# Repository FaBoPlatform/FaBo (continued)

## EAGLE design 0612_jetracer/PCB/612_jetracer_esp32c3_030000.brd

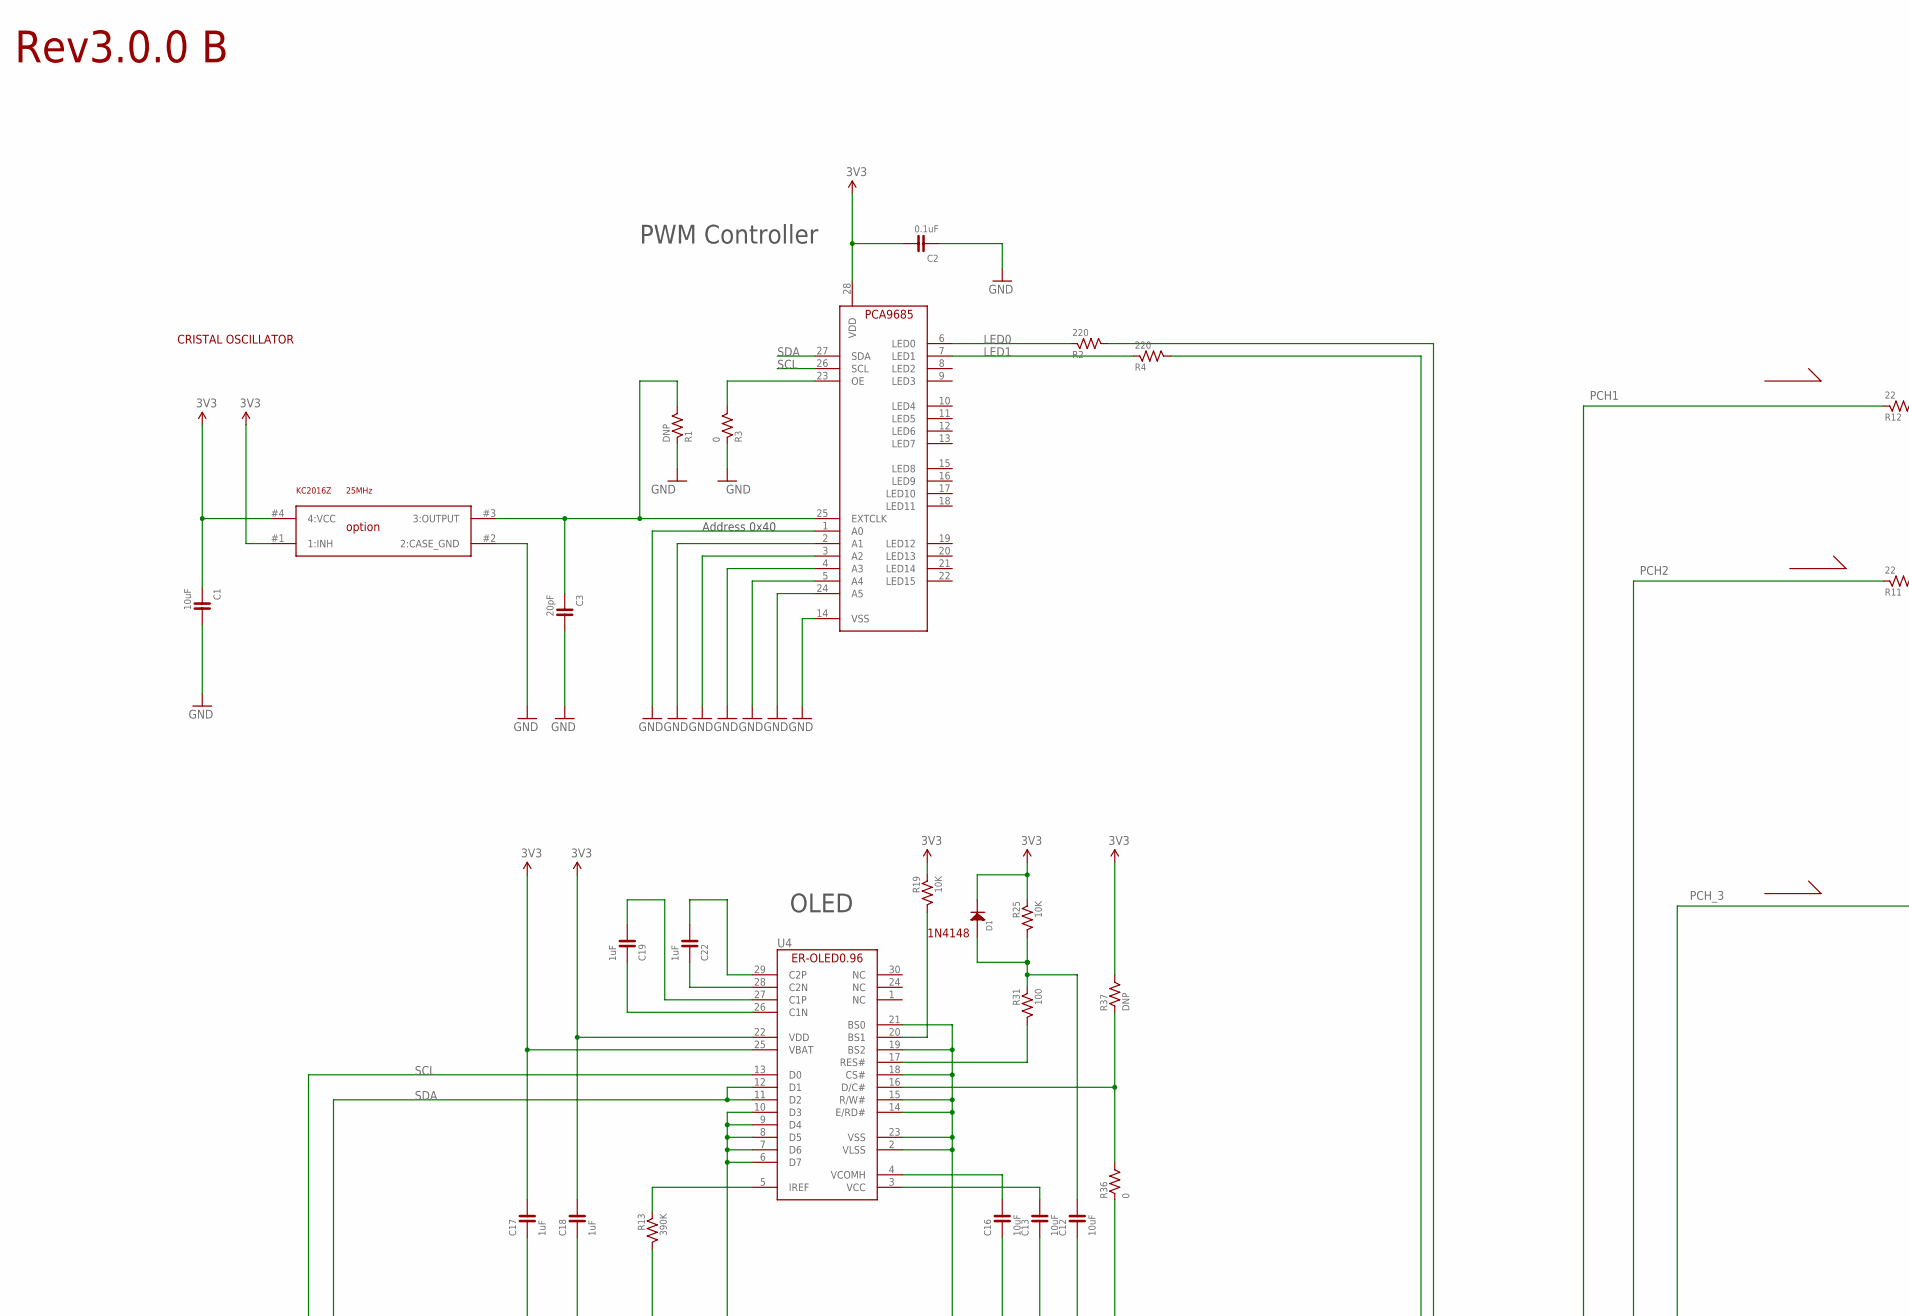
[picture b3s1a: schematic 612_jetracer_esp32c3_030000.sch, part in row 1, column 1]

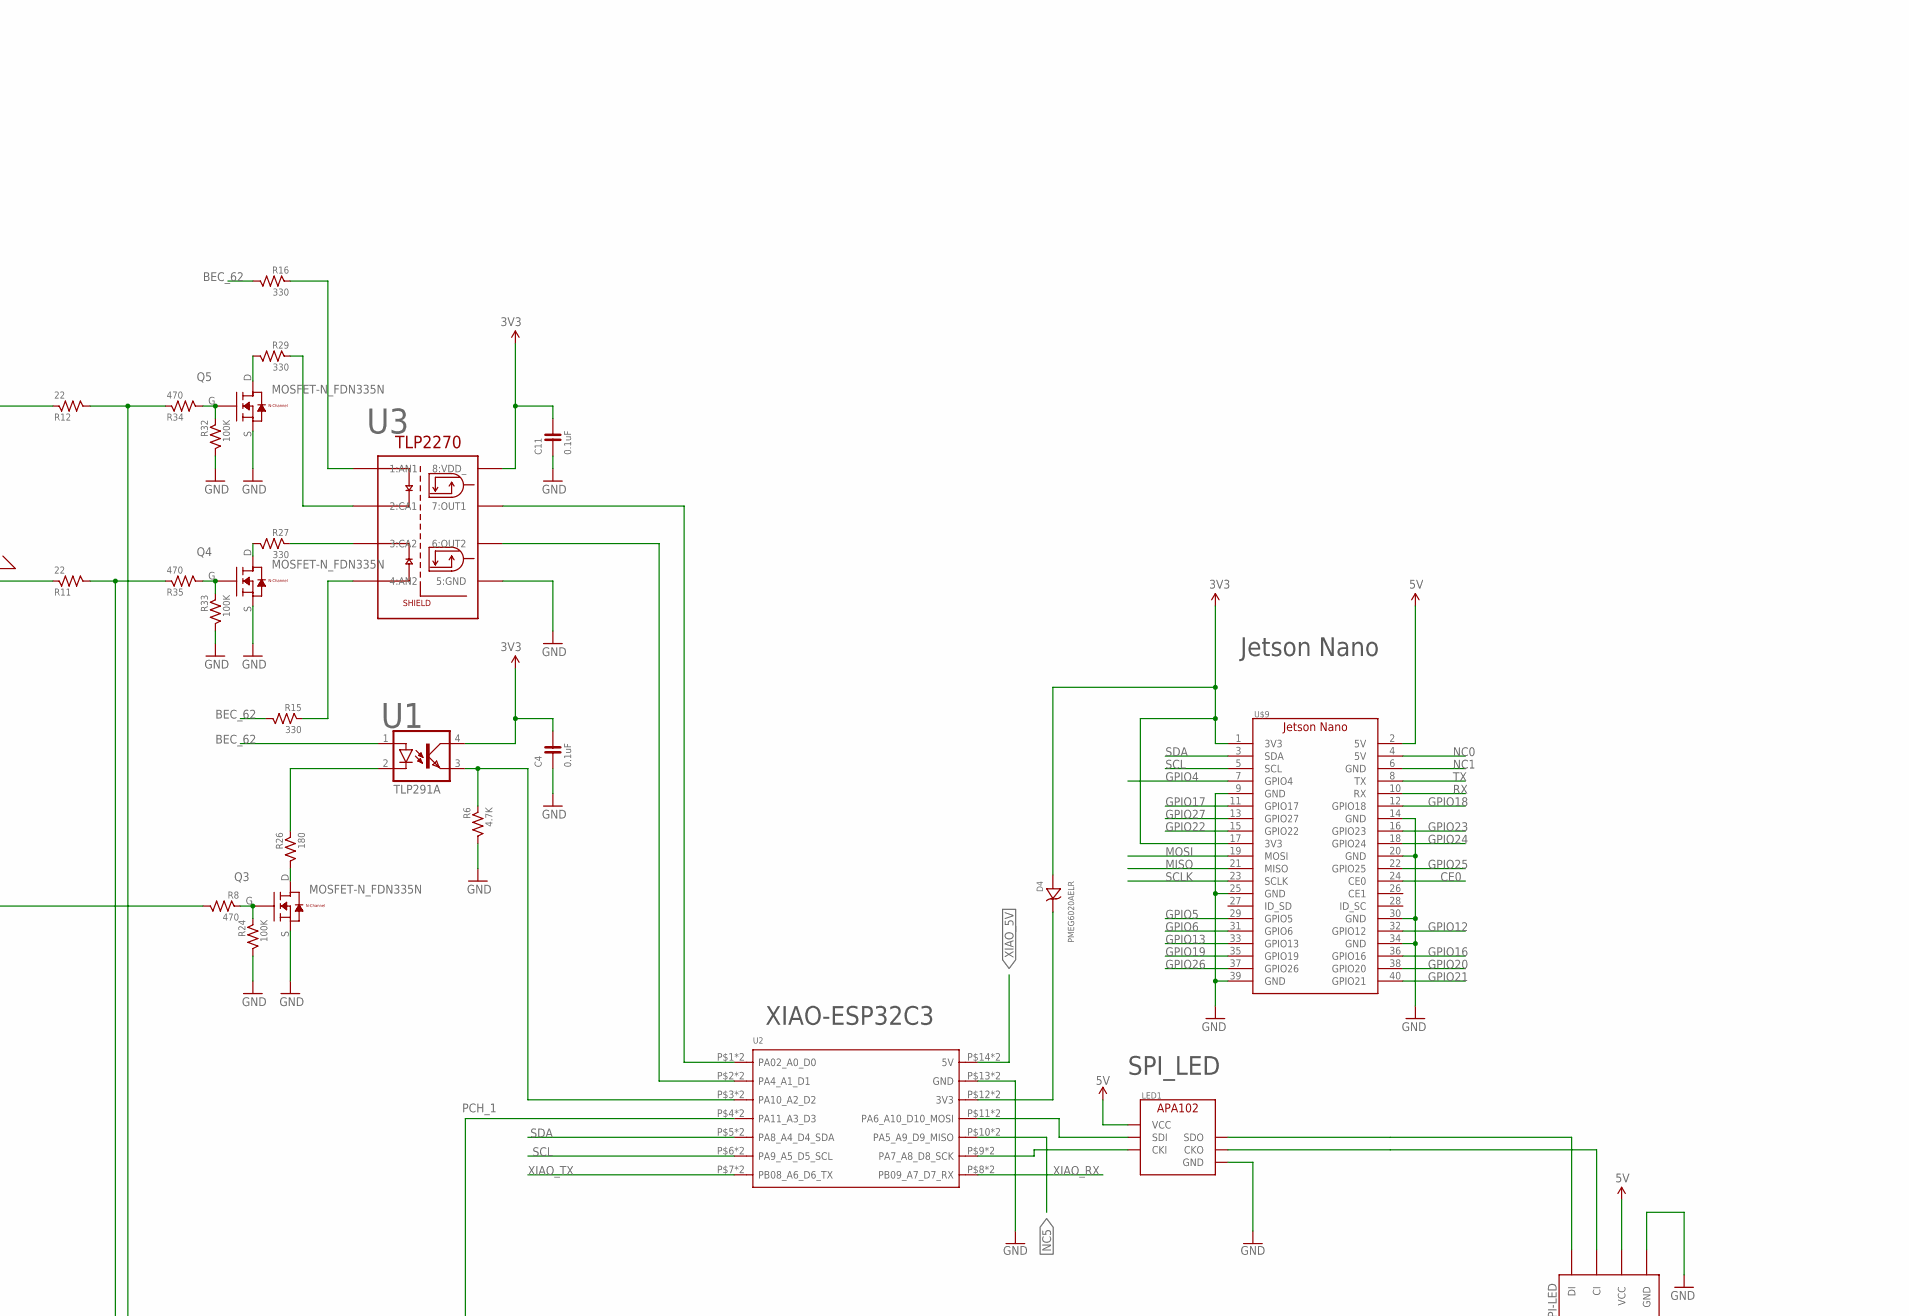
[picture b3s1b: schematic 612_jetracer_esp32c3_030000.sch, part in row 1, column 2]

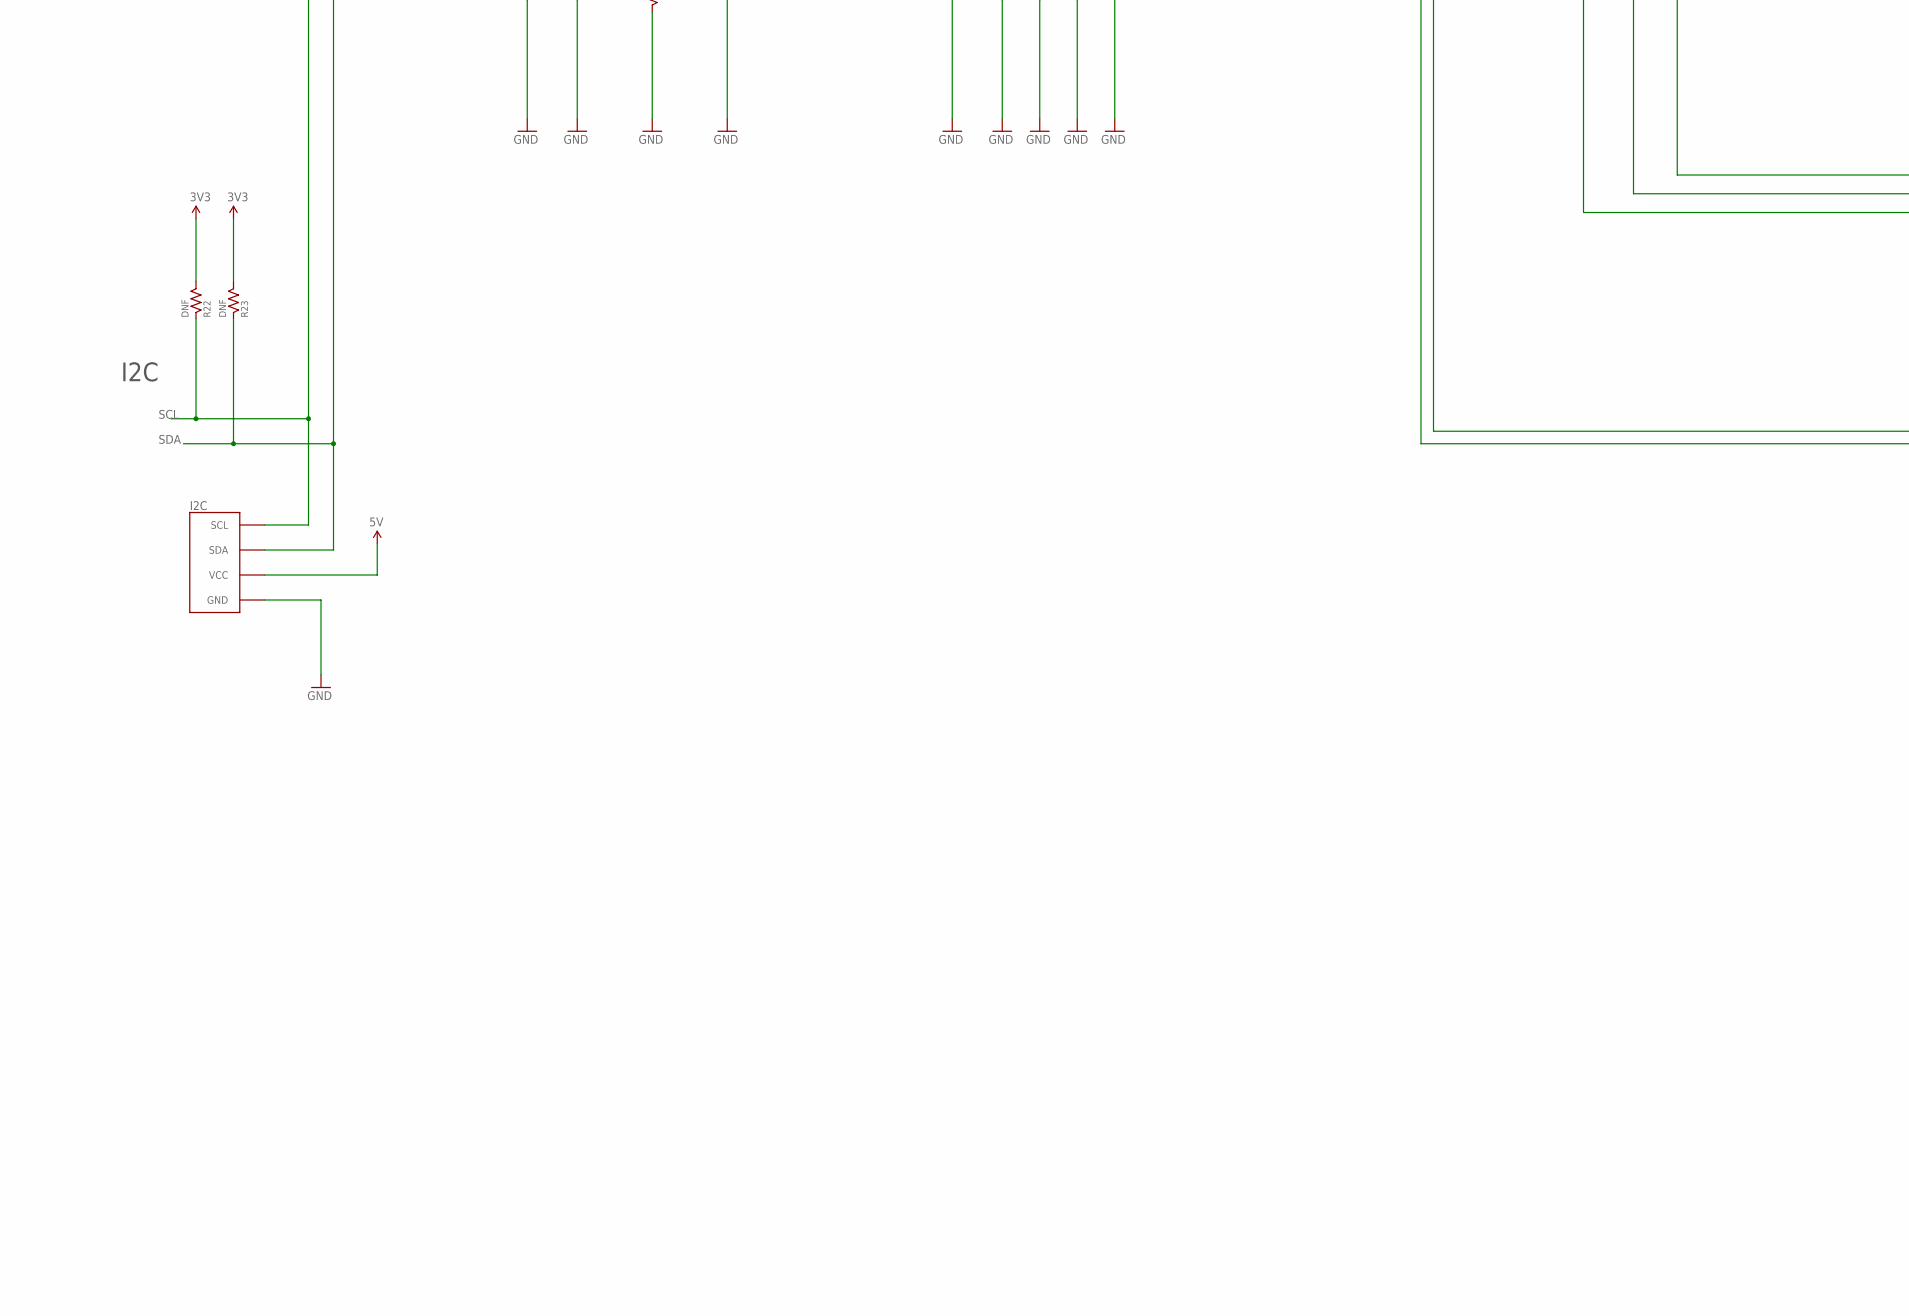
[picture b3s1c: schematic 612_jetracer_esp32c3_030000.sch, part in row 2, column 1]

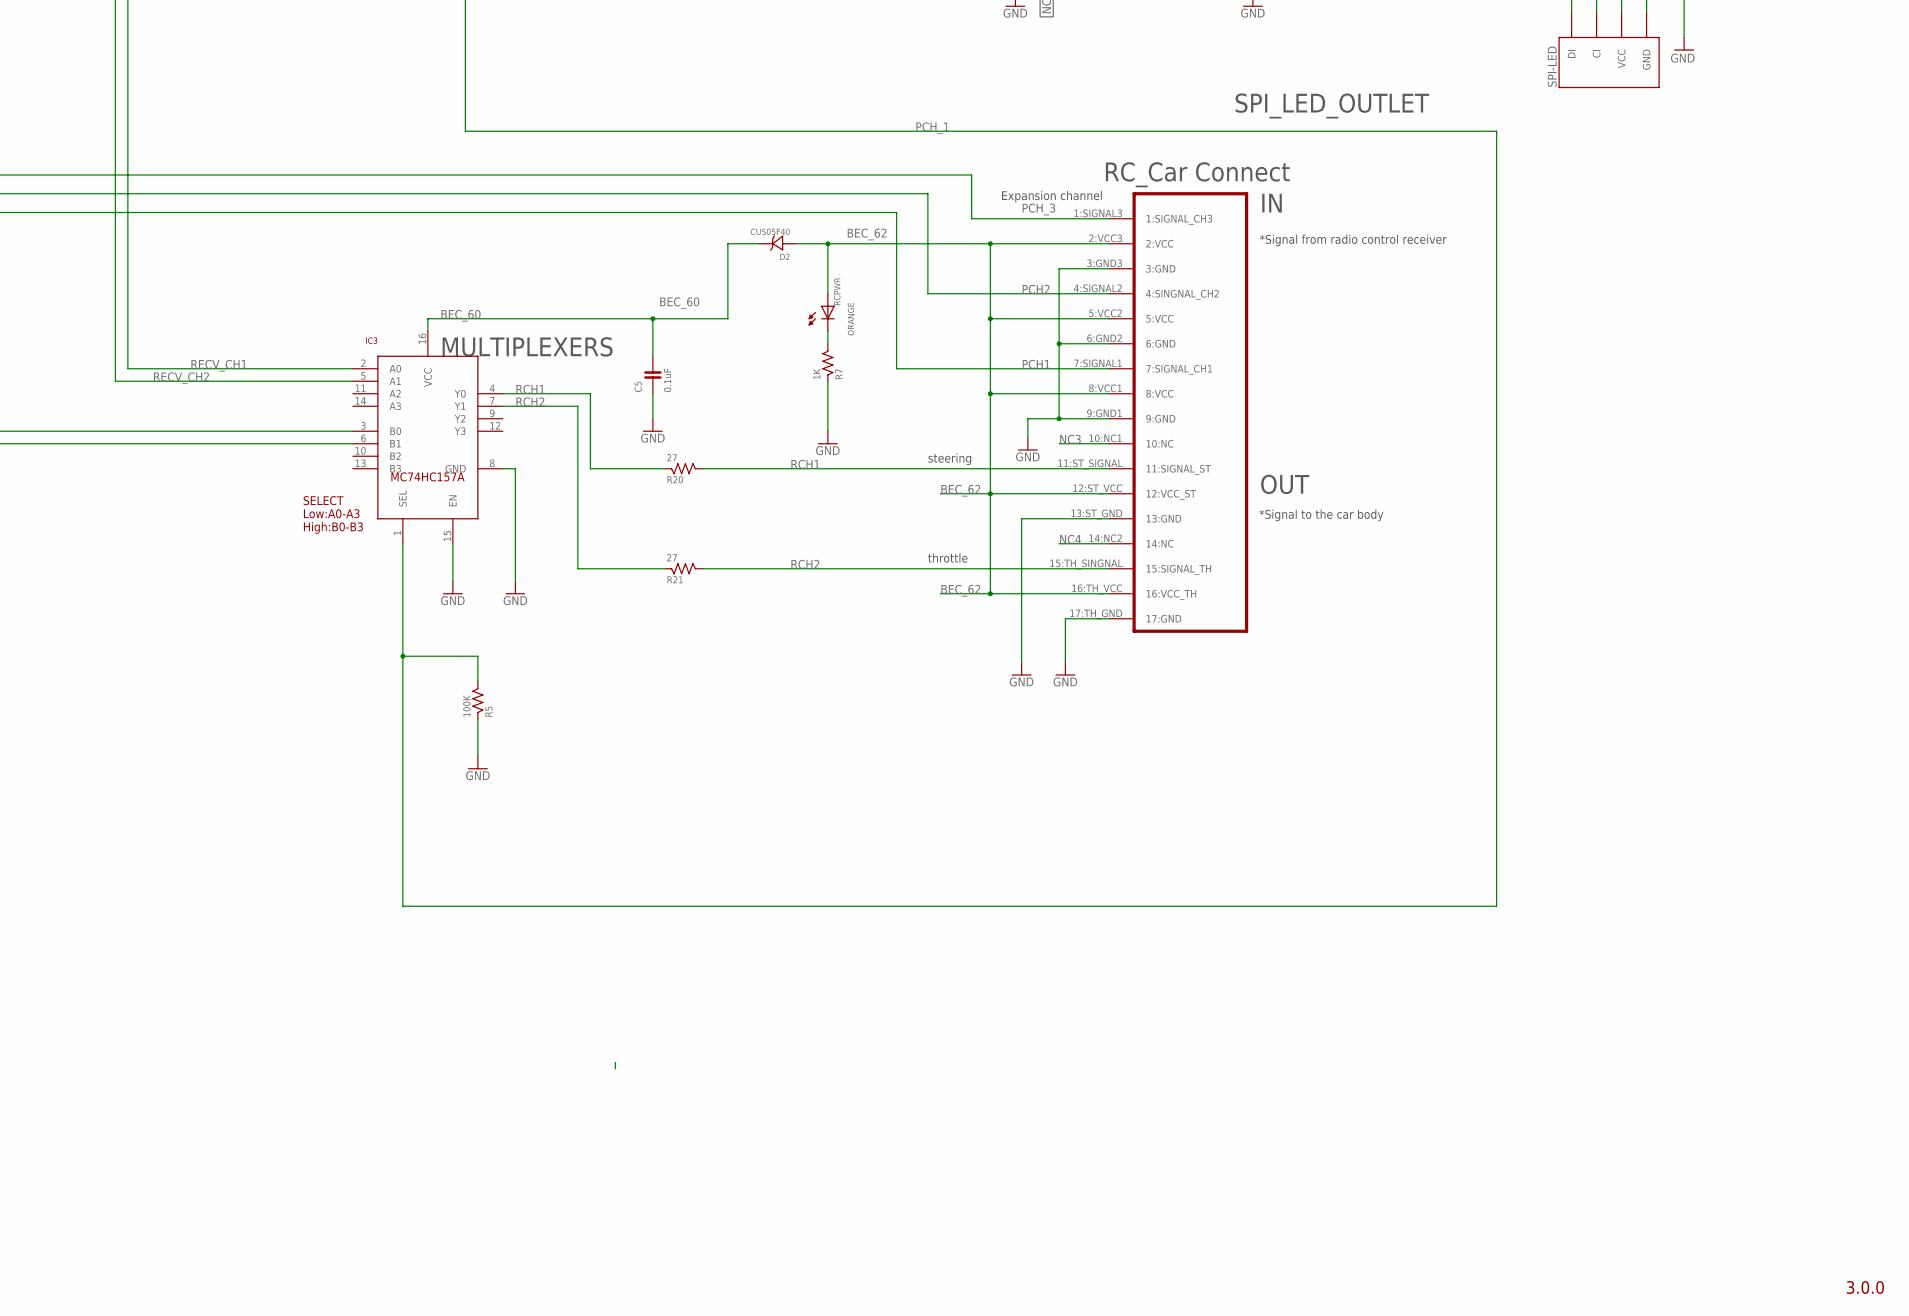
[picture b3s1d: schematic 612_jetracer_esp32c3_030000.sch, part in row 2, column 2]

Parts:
C1, C12, C13, C16: 10uF; 0603
C2, C4, C5, C11: 0.1uF; 0603
C3: 20pF; 0603
C17, C18, C19, C22: 1uF; 0603
D1: 1N4148; 1N4148W
D2: CUS05F40
D4: PMEG6020AELR; SOD123W
I2C: FABO-I2C; I2C-SM04B-PASS-1-FL
IC3: MULTIPLEXERSMC74HC157A; TSSOP-16
IC4: PCA9685_BOTTOM
LED1: APA102_IPIXEL; APA102_2020
Q3, Q4, Q5: MOSFET-N_FDN335N; SUPERSOT-3
R1: DNP; 0603
R2, R4: 220; 0603
R3: 0; 0603
R5, R24, R32, R33: 100K; 0603
R6: 4.7K; 0603
R7: 1K; 0603
R8, R34, R35: 470; 0603
R11, R12: 22; 0603
R13: 390K; 0603
R15, R16, R27, R29: 330; 0603
R19, R25: 10K; 0603
R20, R21: 27; 0603
R22, R23: DNF; 0603
R26: 180; 0603
R31: 100; 0603
R36: 0; 0805
R37: DNP; 0805
RCPWR: ORANGE; 0603
SPI-LED: FABO-SPI-LED; SPI-SM04B-PASS-1-FL
U1: TLP291A; 11-3C1
U2: MOUDLE-SEEEDUINO-XIAO-ESP32C3; MOUDLE14P-DIP
U3: TLP2270
U4: ER-OLED0.96-1ER-CON30HT-1; ER-CON30HT-1
U$1: RC_17PIN_OUTIN; PNHEADER_2.54_SMT_17PIN_RC_TT01_02
U$9: JETSON_NANOJETSON_NANO_OVERALL; JETSON_NANO_DEMENTION
U$11: KC2016Z

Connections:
3V3_JETSON: C1.1, C2.2, C4.2, C11.2, C17.2, C18.2, D1.CATHODE, D4.2 (ANODE), IC4.28 (VDD), R19.1, R22.2, R23.2, R25.1, R37.2, U1.4 (COL), U3.8 (8:VDD_), U4.22 (VDD), U4.25 (VBAT), U$9.1 (3V3), U$9.17 (3V3), U$11.#1 (1:INH), U$11.#4 (4:VCC)
5V_JETSON: I2C.5V (VCC), LED1.VCC, SPI-LED.5V (VCC), U$9.2 (5V)
BEC_60: C5.2, D2.C (CATHODE), IC3.16 (VCC)
BEC_62: D2.A (ANODE), R15.2, R16.2, RCPWR.ANODE, U1.1 (A), U$1.2:VCC3 (2:VCC), U$1.5:VCC2 (5:VCC), U$1.8:VCC1 (8:VCC), U$1.12:ST_VCC (12:VCC_ST), U$1.16:TH_VCC (16:VCC_TH)
CE0: U$9.24 (CE0)
GND: C1.2, C2.1, C3.2, C4.1, C5.1, C11.1, C12.1, C13.1, C16.1, C17.1, C18.1, I2C.GND, IC3.8 (GND), IC3.15 (EN), IC4.1 (A0), IC4.2 (A1), IC4.3 (A2), IC4.4 (A3), IC4.5 (A4), IC4.14 (VSS), IC4.24 (A5), LED1.GND, Q3.S, Q4.S, Q5.S, R1.1, R3.1, R5.1, R6.2, R7.1, R13.2, R24.2, R32.2, R33.2, R36.1, SPI-LED.GND, U2.P$13 (GND), U2.P$27 (GND), U3.5 (5:GND), U4.2 (VLSS), U4.6 (D7), U4.7 (D6), U4.8 (D5), U4.9 (D4), U4.10 (D3), U4.14 (E/RD#), U4.15 (R/W#), U4.18 (CS#), U4.19 (BS2), U4.21 (BS0), U4.23 (VSS), U$1.3:GND3 (3:GND), U$1.6:GND2 (6:GND), U$1.9:GND1 (9:GND), U$1.13:ST_GND (13:GND), U$1.17:TH_GND (17:GND), U$9.9 (GND), U$9.14 (GND), U$9.20 (GND), U$9.25 (GND), U$9.30 (GND), U$9.34 (GND), U$9.39 (GND), U$11.#2 (2:CASE_GND)
GPIO4: U$9.7 (GPIO4)
GPIO5: U$9.29 (GPIO5)
GPIO6: U$9.31 (GPIO6)
GPIO12: U$9.32 (GPIO12)
GPIO13: U$9.33 (GPIO13)
GPIO16: U$9.36 (GPIO16)
GPIO17: U$9.11 (GPIO17)
GPIO18: U$9.12 (GPIO18)
GPIO19: U$9.35 (GPIO19)
GPIO20: U$9.38 (GPIO20)
GPIO21: U$9.40 (GPIO21)
GPIO22: U$9.15 (GPIO22)
GPIO23: U$9.16 (GPIO23)
GPIO24: U$9.18 (GPIO24)
GPIO25: U$9.22 (GPIO25)
GPIO26: U$9.37 (GPIO26)
GPIO27: U$9.13 (GPIO27)
LED0: IC4.6 (LED0), R2.1
LED1: IC4.7 (LED1), R4.1
MISO: U$9.21 (MISO)
MOSI: U$9.19 (MOSI)
unnamed: IC3.6 (B1), R4.2
unnamed: C22.2, U4.29 (C2P)
unnamed: IC3.3 (B0), R2.2
unnamed: U2.P$1 (PA02_A0_D0), U2.P$15 (PA02_A0_D0), U3.7 (7:OUT1)
unnamed: R26.1, U1.2 (C)
unnamed: IC4.23 (OE), R3.2
unnamed: U2.P$2 (PA4_A1_D1), U2.P$16 (PA4_A1_D1), U3.6 (6:OUT2)
unnamed: R15.1, U3.4 (4:AN2)
unnamed: LED1.SDI, U2.P$11 (PA6_A10_D10_MOSI), U2.P$25 (PA6_A10_D10_MOSI)
unnamed: LED1.CKI, U2.P$9 (PA7_A8_D8_SCK), U2.P$23 (PA7_A8_D8_SCK)
unnamed: R16.1, U3.1 (1:AN1)
unnamed: LED1.SDO, SPI-LED.DI
unnamed: R13.1, U4.5 (IREF)
unnamed: LED1.CKO, SPI-LED.CI
unnamed: C19.2, U4.27 (C1P)
unnamed: C13.2, U4.3 (VCC)
unnamed: R31.2, U4.17 (RES#)
unnamed: C19.1, U4.26 (C1N)
unnamed: C22.1, U4.28 (C2N)
unnamed: Q3.G, R8.1, R24.1
unnamed: R7.2, RCPWR.CATHODE
unnamed: C16.2, U4.4 (VCOMH)
unnamed: Q3.D, R26.2
unnamed: Q4.D, R27.2
unnamed: R27.1, U3.3 (3:CA2)
unnamed: Q5.D, R29.2
unnamed: R29.1, U3.2 (2:CA1)
unnamed: C12.2, D1.ANODE, R25.2, R31.1
unnamed: Q5.G, R32.1, R34.2
unnamed: D4.1 (CATHODE), U2.P$12 (3V3), U2.P$26 (3V3)
unnamed: R21.2, U$1.15:TH_SINGNAL (15:SIGNAL_TH)
unnamed: R20.2, U$1.11:ST_SIGNAL (11:SIGNAL_ST)
unnamed: R36.2, R37.1, U4.16 (D/C#)
unnamed: Q4.G, R33.1, R35.2
unnamed: C3.1, IC4.25 (EXTCLK), R1.2, U$11.#3 (3:OUTPUT)
unnamed: R19.2, U4.20 (BS1)
NC0: U$9.4 (5V)
NC1: U$9.6 (GND)
NC3: U$1.10:NC1 (10:NC)
NC4: U$1.14:NC2 (14:NC)
NC5: U2.P$10 (PA5_A9_D9_MISO), U2.P$24 (PA5_A9_D9_MISO)
PCH1: R12.1, U$1.7:SIGNAL1 (7:SIGNAL_CH1)
PCH2: R11.1, U$1.4:SIGNAL2 (4:SINGNAL_CH2)
PCH3_328: R6.1, U1.3 (EMI), U2.P$3 (PA10_A2_D2), U2.P$17 (PA10_A2_D2)
PCH_1: IC3.1 (SEL), R5.2, U2.P$4 (PA11_A3_D3), U2.P$18 (PA11_A3_D3)
PCH_3: R8.2, U$1.1:SIGNAL3 (1:SIGNAL_CH3)
RCH1: IC3.4 (Y0), R20.1
RCH2: IC3.7 (Y1), R21.1
RECV_CH1: IC3.2 (A0), R12.2, R34.1
RECV_CH2: IC3.5 (A1), R11.2, R35.1
RX: U$9.10 (RX)
SCL: I2C.SCL, IC4.26 (SCL), R22.1, U2.P$6 (PA9_A5_D5_SCL), U2.P$20 (PA9_A5_D5_SCL), U4.13 (D0), U$9.5 (SCL)
SCLK: U$9.23 (SCLK)
SDA: I2C.SDA, IC4.27 (SDA), R23.1, U2.P$5 (PA8_A4_D4_SDA), U2.P$19 (PA8_A4_D4_SDA), U4.11 (D2), U4.12 (D1), U$9.3 (SDA)
TX: U$9.8 (TX)
XIAO_5V: U2.P$14 (5V), U2.P$28 (5V)
XIAO_RX: U2.P$8 (PB09_A7_D7_RX), U2.P$22 (PB09_A7_D7_RX)
XIAO_TX: U2.P$7 (PB08_A6_D6_TX), U2.P$21 (PB08_A6_D6_TX)

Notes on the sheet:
3.0.0
Jetson Nano
PWM Controller
Address 0x40
MULTIPLEXERS
*Signal from radio control receiver
*Signal to the car body
steering
throttle
Expansion channel
OUT
SPI_LED_OUTLET
MC74HC157A
SELECT Low:A0-A3 High:B0-B3
RC_Car Connect
option
CRISTAL OSCILLATOR
I2C
1N4148
OLED
Rev3.0.0 B
SPI_LED
XIAO-ESP32C3

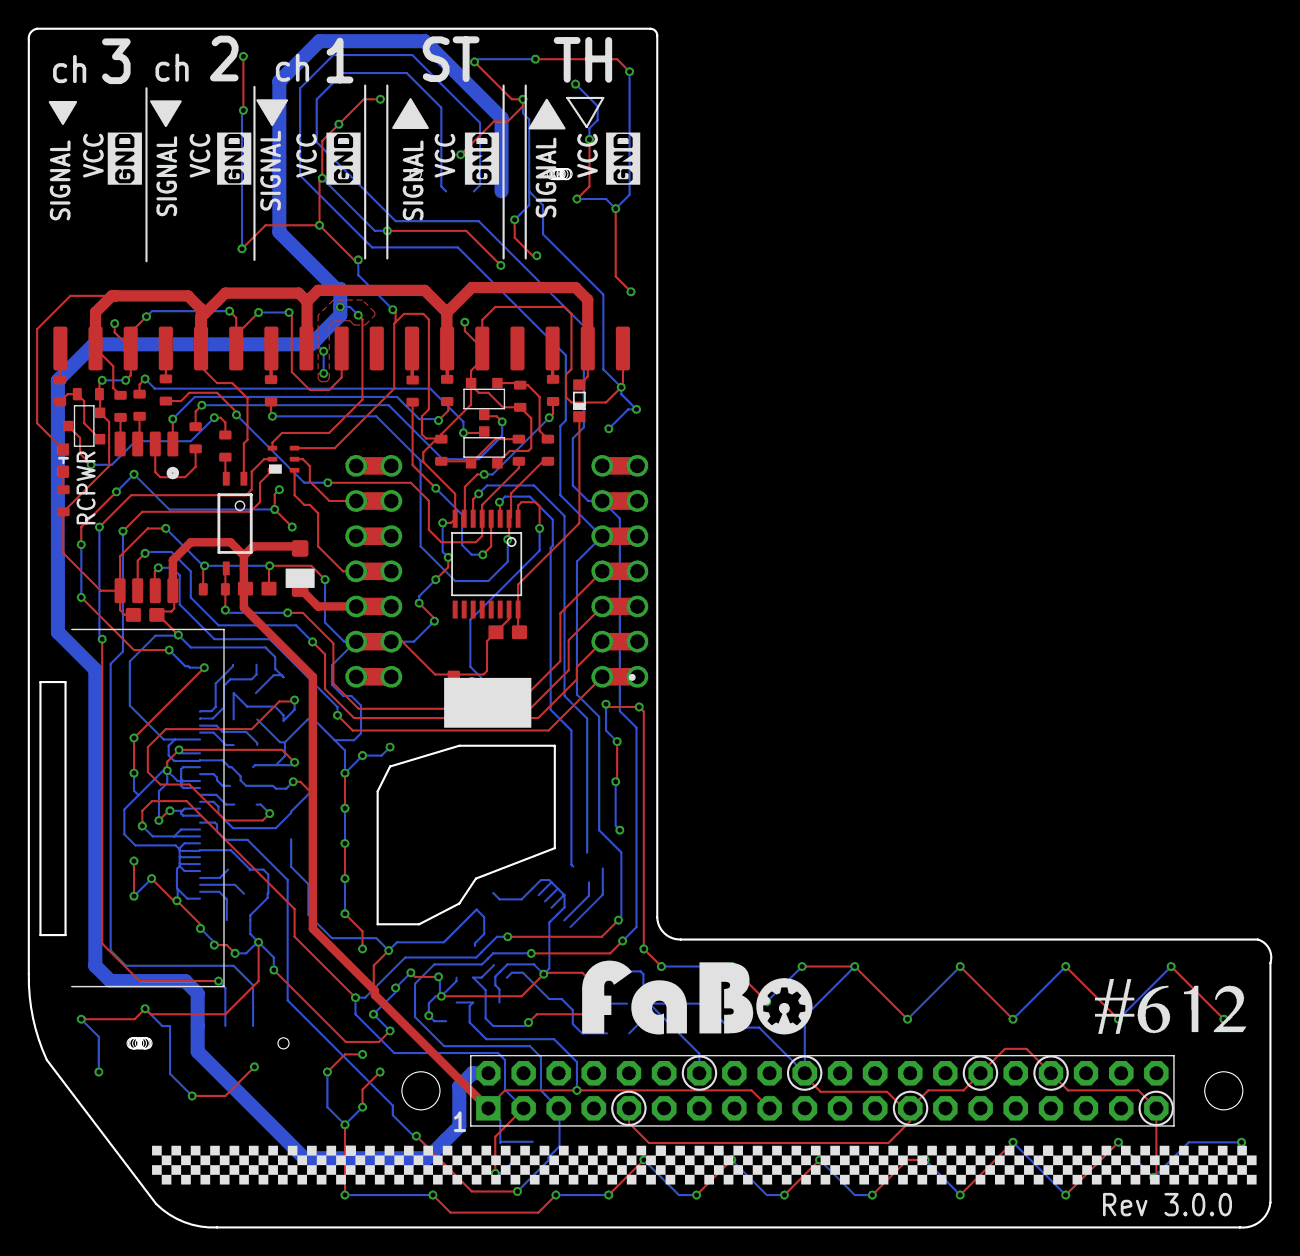
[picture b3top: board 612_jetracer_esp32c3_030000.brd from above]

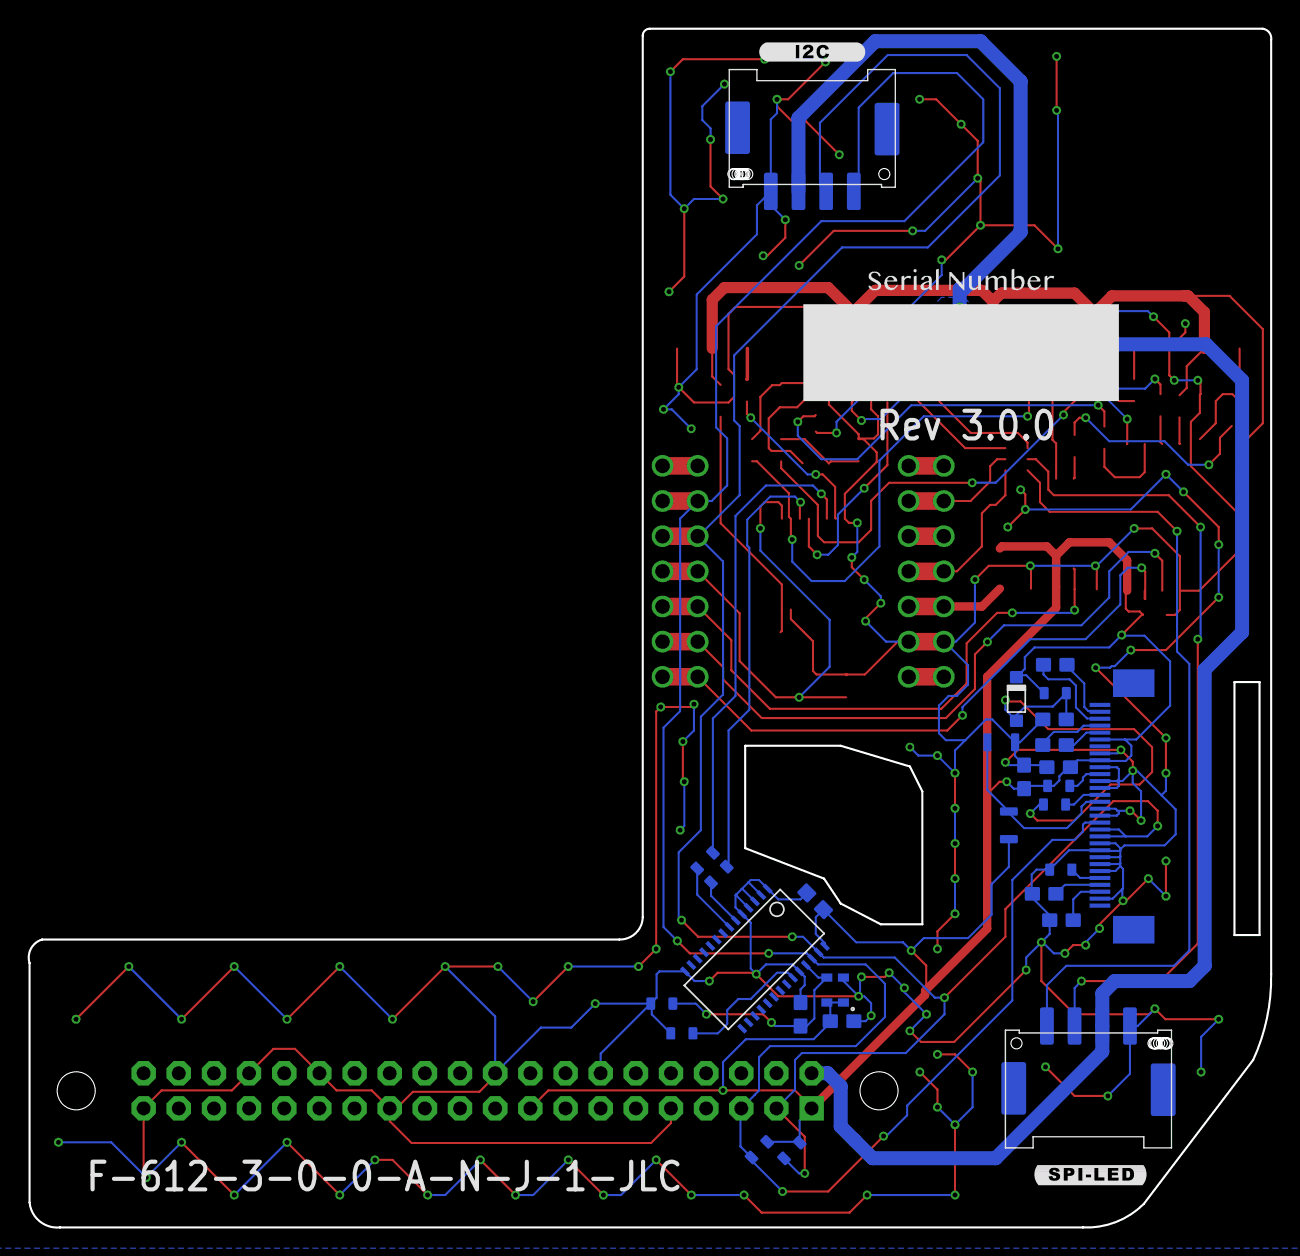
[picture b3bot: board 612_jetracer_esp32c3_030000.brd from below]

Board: 2 copper layers, 89.8 x 86.6 mm, 68 parts (26 on the bottom side), 58 nets.

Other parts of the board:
U$2: LOGO_FABO_L
U$5, U$6, U$7, U$8, U$12: LOGO_SILK_GND
